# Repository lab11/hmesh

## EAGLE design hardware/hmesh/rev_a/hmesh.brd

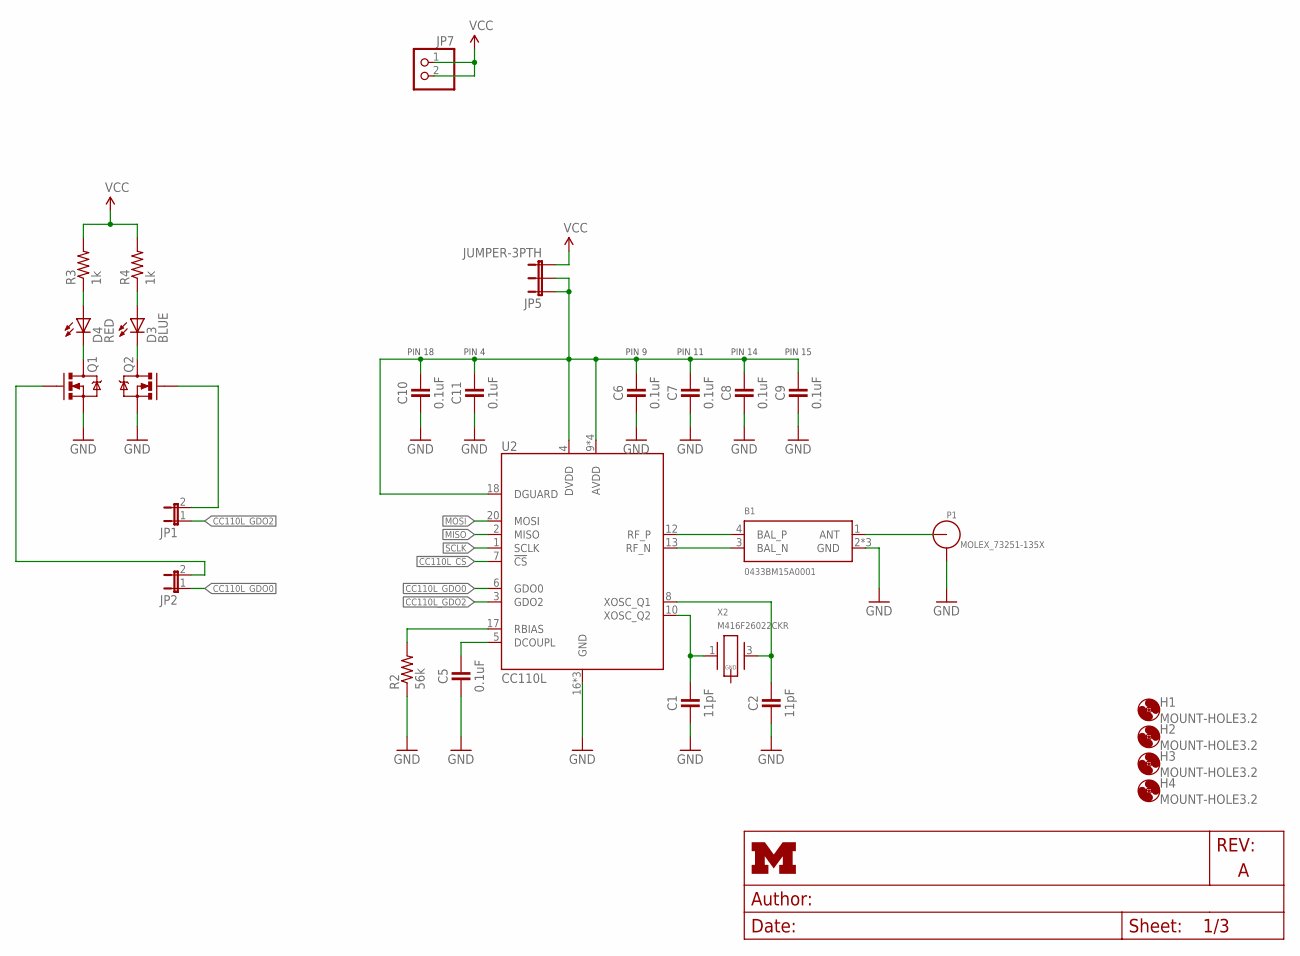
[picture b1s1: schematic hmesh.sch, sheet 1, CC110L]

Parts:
B1: 0433BM15A0001; 2450BM
C1, C2: 11pF; 0402_CAP; DIGIKEY 490-5923-1-ND
C5, C6, C7, C8, C9, C10, C11: 0.1uF; 0402_CAP; DIGIKEY 445-1265-1-ND
D3: BLUE; LED-0603
D4: RED; LED-0603
H1, H2, H3, H4: MOUNT-HOLE3.2; 3,2
JP1, JP2: JUMPER-2PTH; 1X02
JP5: JUMPER-3PTH; 1X03
JP7: PINHD-1X2; 1X02
P1: MOLEX_73251-135X; SMA-J/PCB
Q1, Q2: MOSFET-NCHANNELSMD; SOT23-3; DIGIKEY 568-5818-1-ND
R2: 56k; 0402_RES; DIGIKEY RHM56KBHCT-ND
R3, R4: 1k; 0402_RES
U2: CC110L; S-PVQFN-N20
X2: M416F26022CKR; M416

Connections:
!CC110L_CS: U2.7 (!CS); also elsewhere on the board
CC110L_GDO0: JP2.1, U2.6 (GDO0); also elsewhere on the board
CC110L_GDO2: JP1.1, U2.3 (GDO2); also elsewhere on the board
GND: B1.2 (GND), B1.5 (GND), B1.6 (GND), C1.2, C2.2, C5.2, C6.2, C7.2, C8.2, C9.2, C10.2, C11.2, P1.2, P1.3, P1.4, P1.5, Q1.2 (S), Q2.2 (S), R2.1, U2.16 (GND), U2.19 (GND), U2.PAD (GND); also elsewhere on the board
MISO: U2.2 (MISO); also elsewhere on the board
MOSI: U2.20 (MOSI); also elsewhere on the board
unnamed: B1.4 (BAL_P), U2.12 (RF_P)
unnamed: B1.3 (BAL_N), U2.13 (RF_N)
unnamed: B1.1 (ANT), P1.1 (ANT)
unnamed: C1.1, U2.10 (XOSC_Q2), X2.1
unnamed: C2.1, U2.8 (XOSC_Q1), X2.3 (2)
unnamed: C5.1, U2.5 (DCOUPL)
unnamed: R2.2, U2.17 (RBIAS)
unnamed: D4.C, Q1.3 (D)
unnamed: D3.C, Q2.3 (D)
unnamed: JP2.2, Q1.1 (G)
unnamed: JP1.2, Q2.1 (G)
unnamed: D4.A, R3.1
unnamed: D3.A, R4.1
SCLK: U2.1 (SCLK); also elsewhere on the board
VCC: JP5.3, JP7.1, JP7.2, R3.2, R4.2; also elsewhere on the board
VCC_CC110L: C6.1, C7.1, C8.1, C9.1, C10.1, C11.1, JP5.1, JP5.2, U2.4 (DVDD), U2.9 (AVDD), U2.11 (AVDD), U2.14 (AVDD), U2.15 (AVDD), U2.18 (DGUARD)

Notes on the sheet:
PIN 9
PIN 11
PIN 14
PIN 15
PIN 4
PIN 18

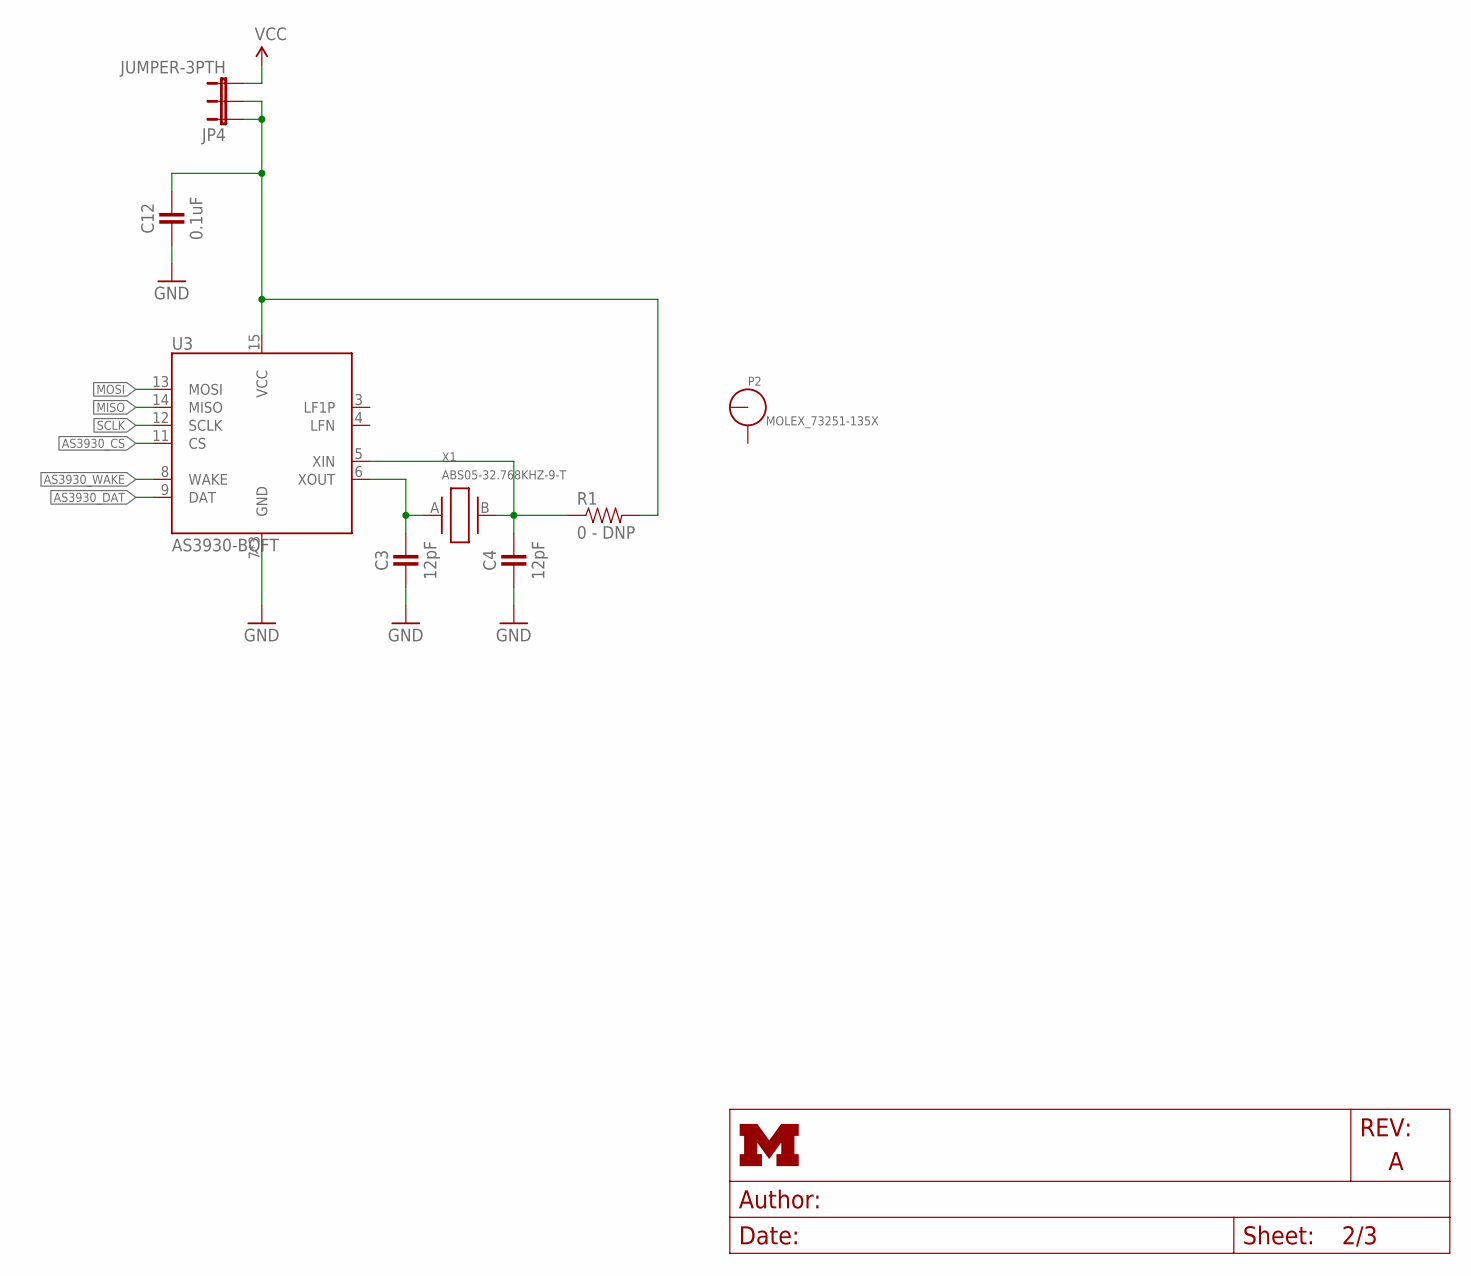
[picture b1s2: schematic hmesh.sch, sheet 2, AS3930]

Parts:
C3, C4: 12pF; 0402_CAP; DIGIKEY 490-6197-1-ND
C12: 0.1uF; 0402_CAP; DIGIKEY 445-1265-1-ND
JP4: JUMPER-3PTH; 1X03
P2: MOLEX_73251-135X; SMA-J/PCB
R1: 0 - DNP; 0603-RES
U3: AS3930-BQFT; QFN-16-4MM
X1: ABS05-32.768KHZ-9-T; ABS05

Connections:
AS3930_CS: U3.11 (CS); also elsewhere on the board
AS3930_DAT: U3.9 (DAT); also elsewhere on the board
AS3930_WAKE: U3.8 (WAKE); also elsewhere on the board
GND: C3.2, C4.2, C12.2, U3.7 (GND), U3.16 (GND), U3.GND; also elsewhere on the board
MISO: U3.14 (MISO); also elsewhere on the board
MOSI: U3.13 (MOSI); also elsewhere on the board
unnamed: C3.1, U3.6 (XOUT), X1.A (1)
unnamed: C4.1, R1.1, U3.5 (XIN), X1.B (2)
SCLK: U3.12 (SCLK); also elsewhere on the board
VCC: JP4.3; also elsewhere on the board
VCC_AS3930: C12.1, JP4.1, JP4.2, R1.2, U3.15 (VCC)

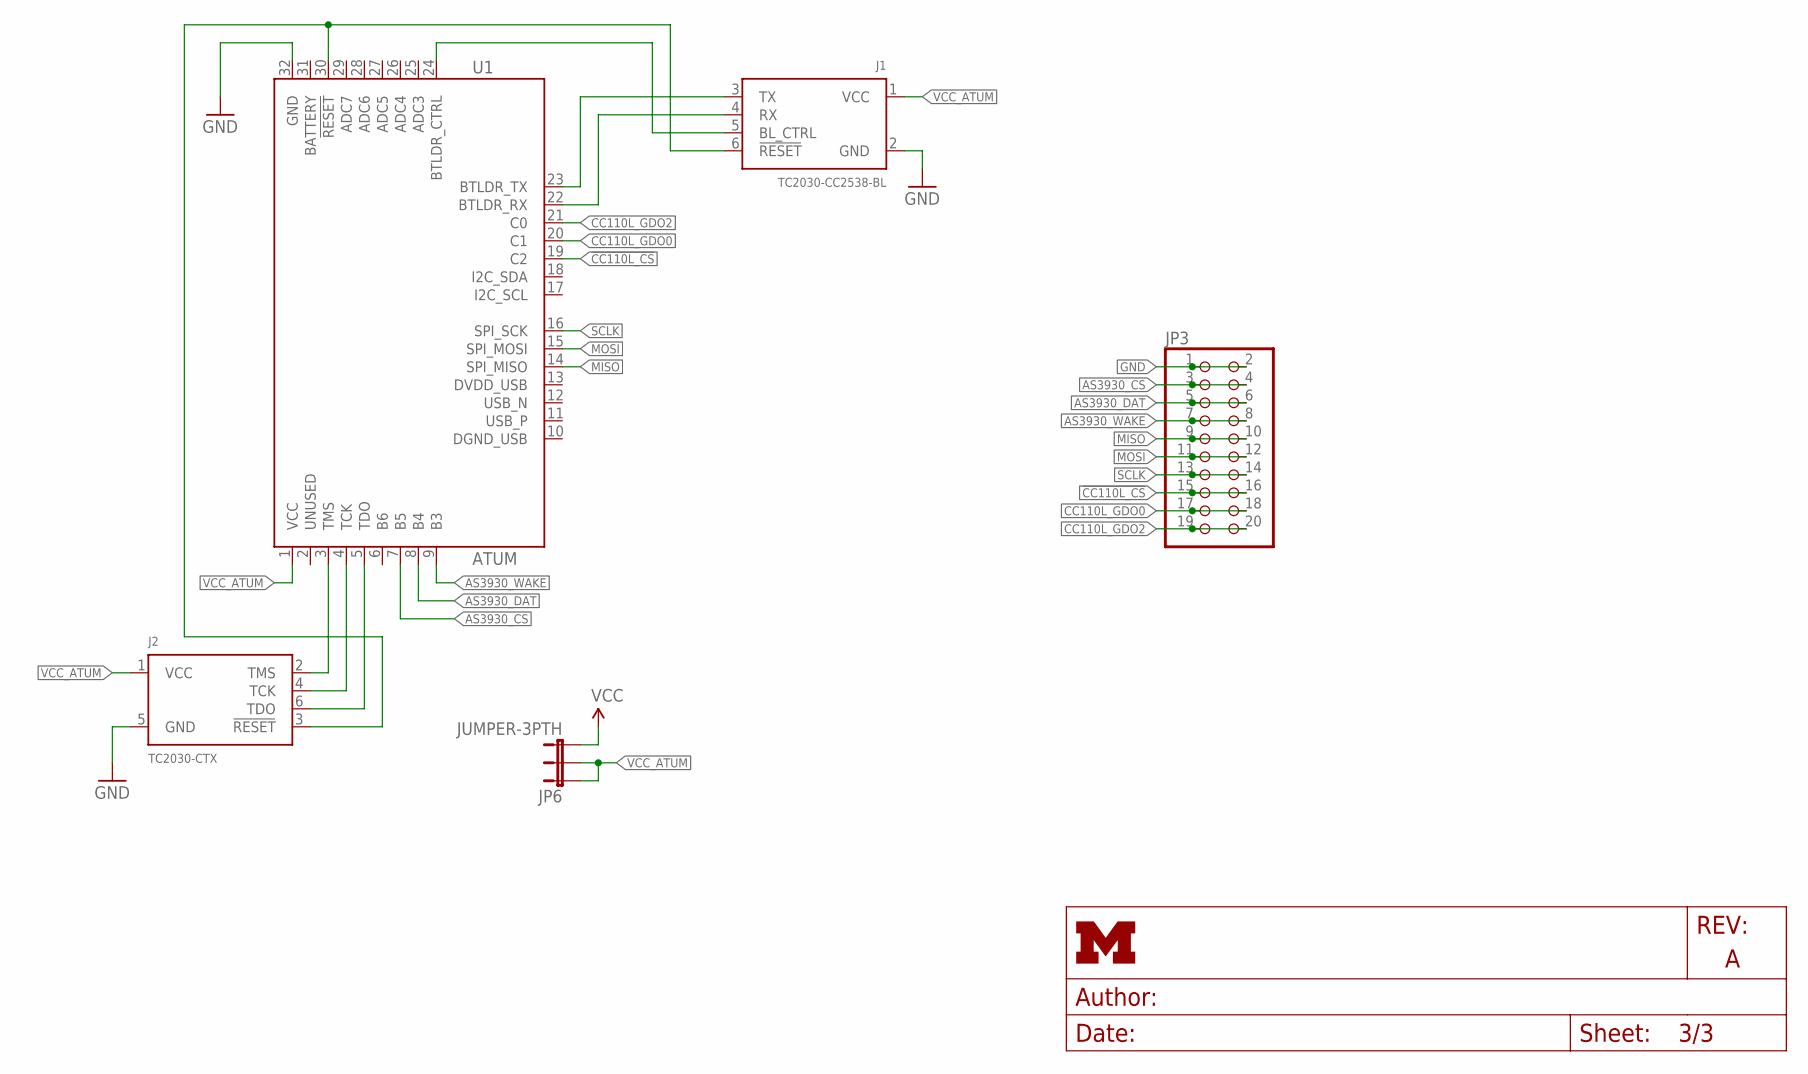
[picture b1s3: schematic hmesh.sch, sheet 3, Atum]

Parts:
J1: TC2030-CC2538-BL; TC2030-IDC
J2: TC2030-CTX; TC2030-IDC
JP3: PINHD-2X10; 2X10
JP6: JUMPER-3PTH; 1X03
U1: ATUM

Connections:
!CC110L_CS: JP3.15, JP3.16, U1.19 (C2); also elsewhere on the board
AS3930_CS: JP3.3, JP3.4, U1.7 (B5); also elsewhere on the board
AS3930_DAT: JP3.5, JP3.6, U1.8 (B4); also elsewhere on the board
AS3930_WAKE: JP3.7, JP3.8, U1.9 (B3); also elsewhere on the board
CC110L_GDO0: JP3.17, JP3.18, U1.20 (C1); also elsewhere on the board
CC110L_GDO2: JP3.19, JP3.20, U1.21 (C0); also elsewhere on the board
GND: J1.2 (GND), J2.5 (GND), JP3.1, JP3.2, U1.32 (GND); also elsewhere on the board
MISO: JP3.9, JP3.10, U1.14 (SPI_MISO); also elsewhere on the board
MOSI: JP3.11, JP3.12, U1.15 (SPI_MOSI); also elsewhere on the board
unnamed: J1.3 (TX), U1.23 (BTLDR_TX)
unnamed: J1.4 (RX), U1.22 (BTLDR_RX)
unnamed: J1.5 (BL_CTRL), U1.24 (BTLDR_CTRL)
unnamed: J1.6 (!RESET), J2.3 (!RESET), U1.30 (!RESET)
unnamed: J2.2 (TMS), U1.3 (TMS)
unnamed: J2.4 (TCK), U1.4 (TCK)
unnamed: J2.6 (TDO), U1.5 (TDO)
SCLK: JP3.13, JP3.14, U1.16 (SPI_SCK); also elsewhere on the board
VCC: JP6.3; also elsewhere on the board
VCC_ATUM: J1.1 (VCC), J2.1 (VCC), JP6.1, JP6.2, U1.1 (VCC)

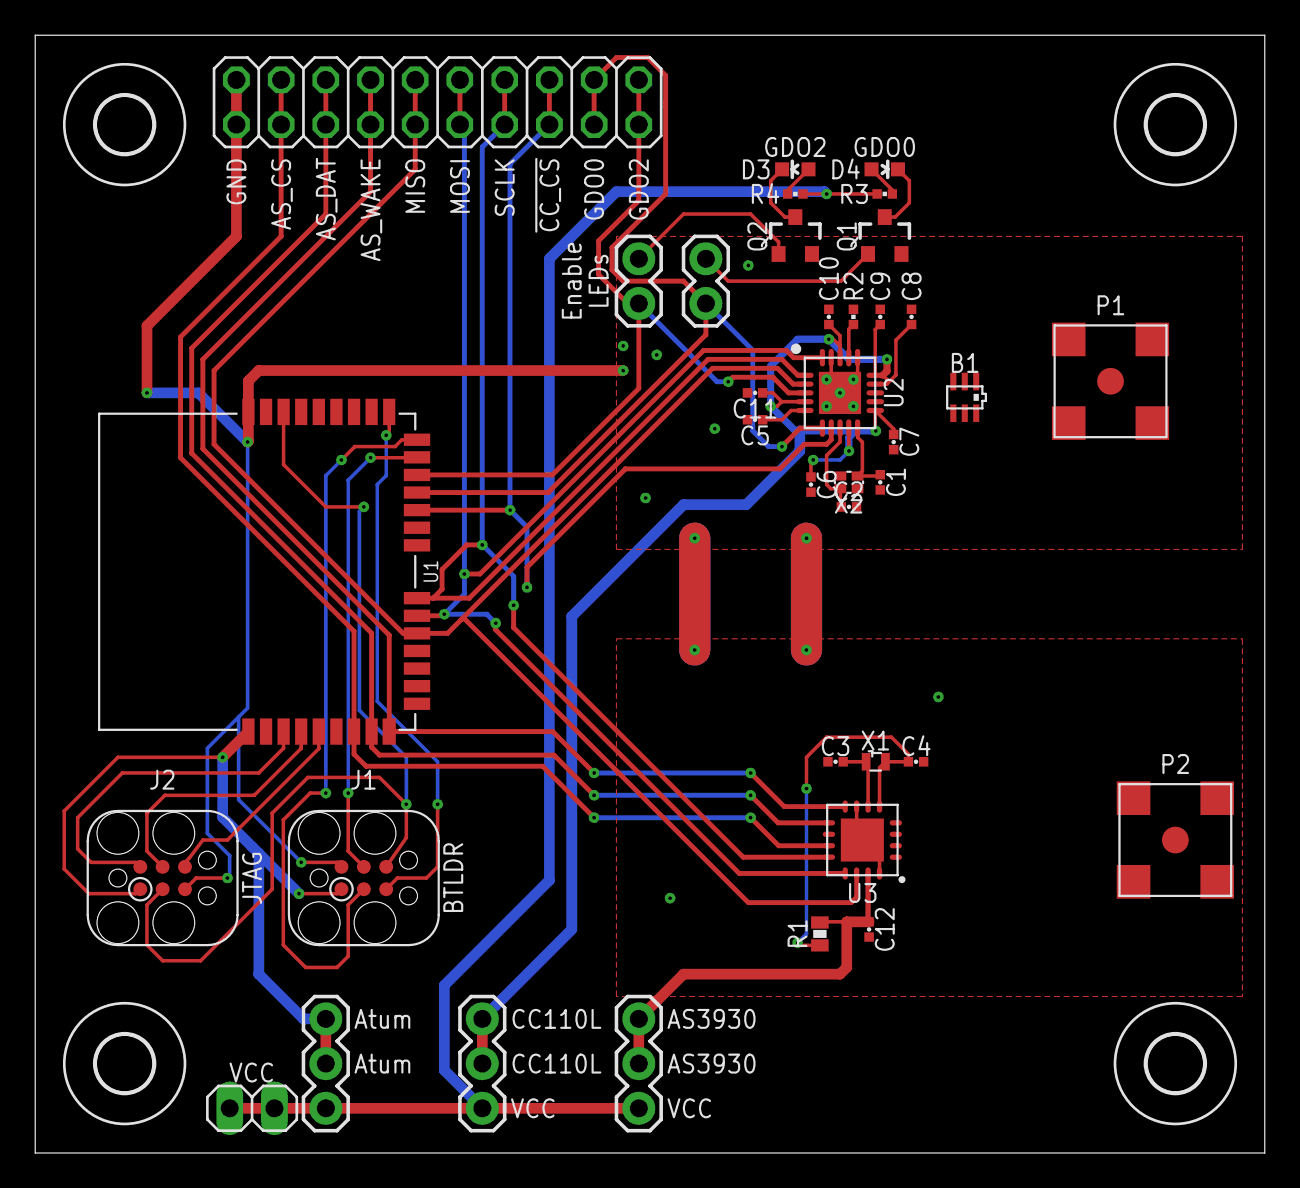
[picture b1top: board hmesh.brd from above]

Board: 2 copper layers, 69.8 x 63.5 mm, 41 parts (0 on the bottom side), 36 nets.

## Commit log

2015-11-17 added relevant papers
2015-11-18 start of schematic
2015-11-18 updated schematic
2015-11-18 pretty good board made
2015-11-18 gitignore

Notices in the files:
parts and their libraries:
SparkFun-LED: Licensing: CC v3.0 Share-Alike You are welcome to use this library for commercial purposes.
